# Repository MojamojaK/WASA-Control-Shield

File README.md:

# WASA-Control-Shield
Kicad Control Shield for WASA HPA project

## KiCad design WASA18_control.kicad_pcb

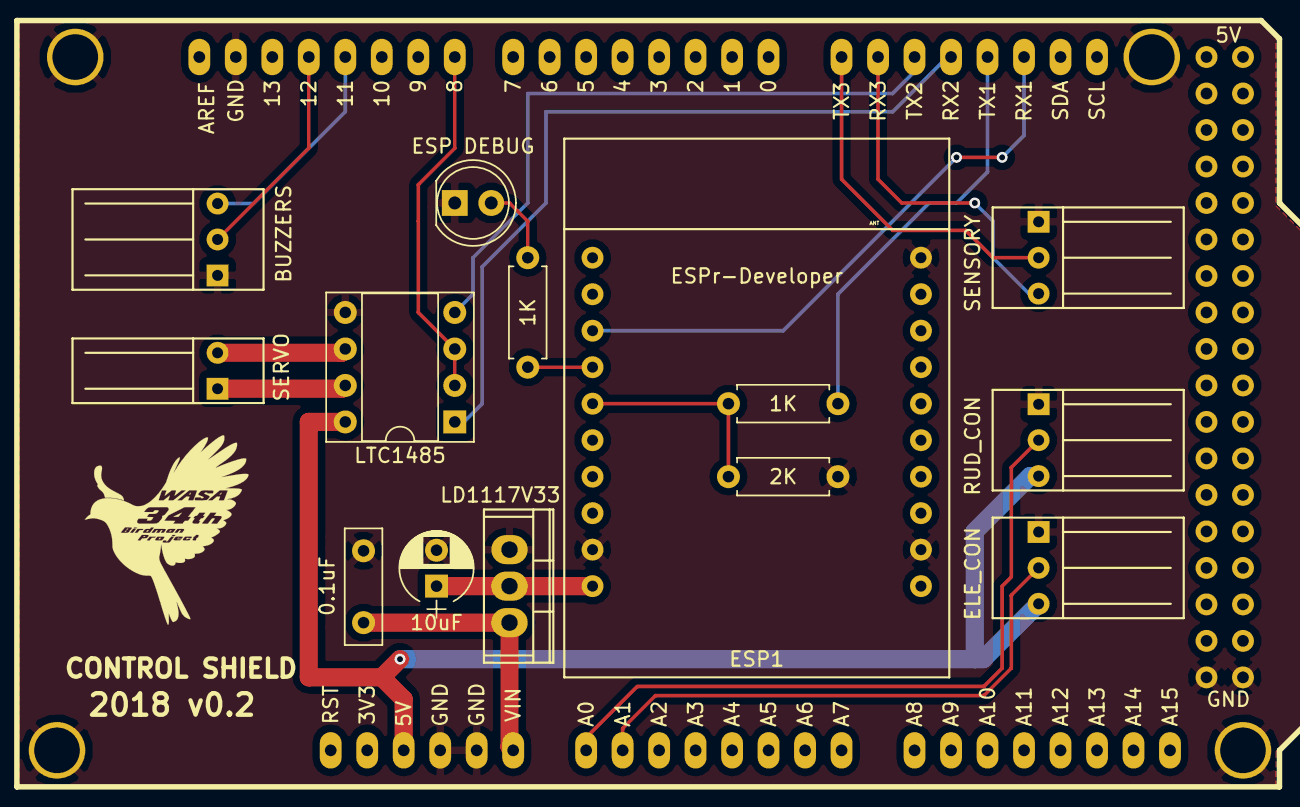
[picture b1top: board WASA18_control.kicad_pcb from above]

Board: 2 copper layers, 15 parts (0 on the bottom side), 20 nets.

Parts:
0.1uF: 100nF; C_Disc_D8.0mm_W2.5mm_P5.00mm
1K, 1K#2: 1K; R_Axial_DIN0207_L6.3mm_D2.5mm_P7.62mm_Horizontal
2K: 2K; R_Axial_DIN0207_L6.3mm_D2.5mm_P7.62mm_Horizontal
10uF: 10uF; CP_Radial_D5.0mm_P2.50mm
BUZZERS: CONN_01X03; Molex-5046-P2.50mm-0x03
CONTROL SHIELD: ARDUINO_MEGA_SHIELD; ARDUINO_MEGA_SHIELD_94.49x53.34
ELE_CON: CONN_01X03; Molex-5046-P2.50mm-0x03
ESP1: ESP-WROOM-02; ESPr_developer_Footprint
ESP DEBUG: LED; LED_D5.0mm
LD1117V33: LD1117V33; TO-220
LTC1485: LTC1485; DIP-8_W7.62mm_Socket
RUD_CON: CONN_01X03; Molex-5046-P2.50mm-0x03
SENSORY: CONN_01X03; Molex-5046-P2.50mm-0x03
SERVO: CONN_01X02; Molex-5046-P2.50mm-0x02

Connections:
5V: CONTROL SHIELD.5V, ELE_CON.3, LTC1485.8, RUD_CON.3
A: LTC1485.6, SERVO.2
B: LTC1485.7, SERVO.1
BUZZER1: BUZZERS.2, CONTROL SHIELD.12
BUZZER2: BUZZERS.3, CONTROL SHIELD.11
ELE_SIG: CONTROL SHIELD.AD1, ELE_CON.2
ESP_LED: 1K#2.1, ESP1.4
ESP_RX: CONTROL SHIELD.19, ESP1.3
ESP_TX3V3: 1K.1, 2K.2, ESP1.5
ESP_TX5V: 1K.2, CONTROL SHIELD.18
GND: 0.1uF.2, 2K.1, 10uF.2, BUZZERS.1, CONTROL SHIELD.GND1, CONTROL SHIELD.GND2, CONTROL SHIELD.GND3, CONTROL SHIELD.GND4, CONTROL SHIELD.GND5, ELE_CON.1, ESP1.9, ESP1.11, ESP1.19, ESP DEBUG.1, LD1117V33.1, LTC1485.5, RUD_CON.1, SENSORY.1
unnamed: 1K#2.2, ESP DEBUG.2
REG_3V3: 10uF.1, ESP1.10, LD1117V33.2
RUD_SIG: CONTROL SHIELD.AD0, RUD_CON.2
SENSOR_RX: CONTROL SHIELD.15, SENSORY.3
SENSOR_TX: CONTROL SHIELD.14, SENSORY.2
SERVO_EN: CONTROL SHIELD.8, LTC1485.2, LTC1485.3
SERVO_RX: CONTROL SHIELD.17, LTC1485.1
SERVO_TX: CONTROL SHIELD.16, LTC1485.4
VIN: 0.1uF.1, CONTROL SHIELD.V_IN, LD1117V33.3

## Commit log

2018-03-03 Updated With .gitignore
2018-03-03 Removed temporary files
2018-03-03 Create LICENSE
